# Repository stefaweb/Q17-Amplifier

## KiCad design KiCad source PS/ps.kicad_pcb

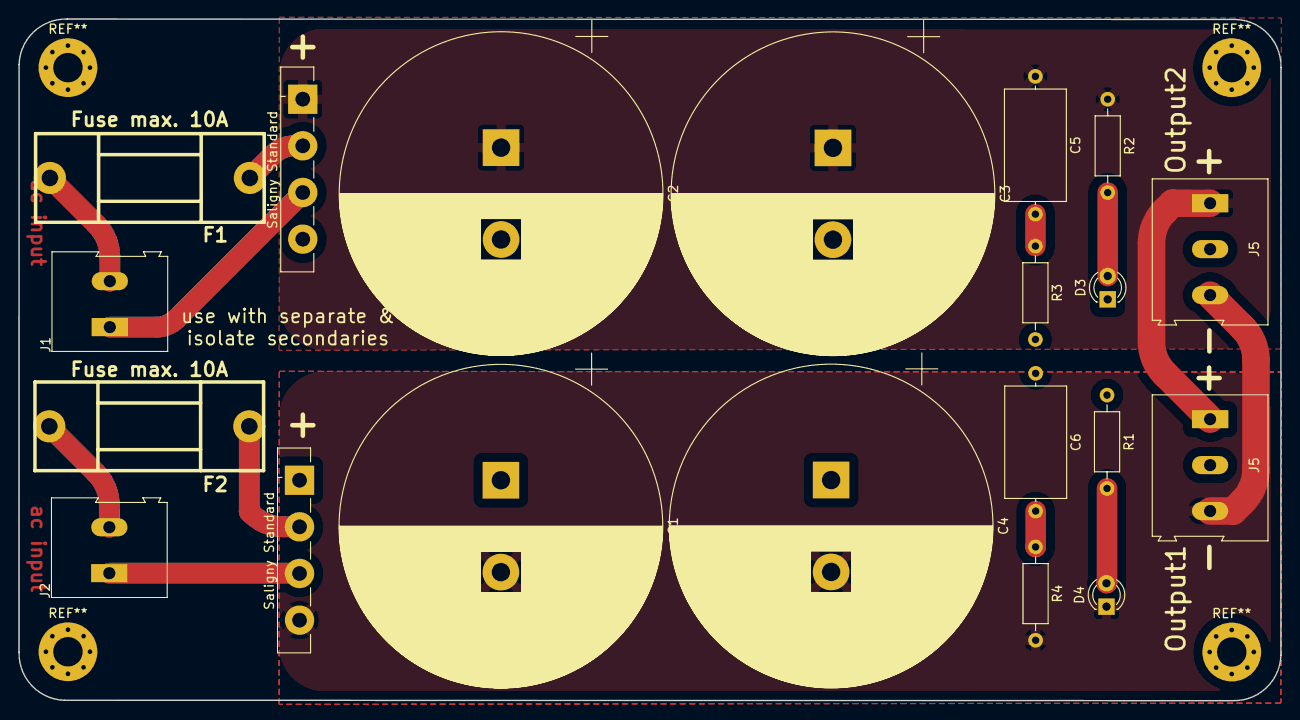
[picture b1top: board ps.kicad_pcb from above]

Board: 2 copper layers, 137.4 x 74.2 mm, 20 parts (0 on the bottom side), 11 nets.

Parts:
C1, C2, C3, C4: C_Polarized; CP_Radial_D35.0mm_P10.00mm_SnapIn
C5, C6: 220nF; C_Axial_L12.0mm_D6.5mm_P15.00mm_Horizontal
D3, D4: LED; LED_D3.0mm
F1, F2: Fuse max. 10A; fuse_holder_CQ-2
J1, J2: Conn_01x02_Female; TerminalBlock_Altech_AK300-2_P5.00mm
J5, J5#2: Conn_01x03_Female; TerminalBlock_Altech_AK300-3_P5.00mm
R1, R2: 10K; R_Axial_DIN0207_L6.3mm_D2.5mm_P10.16mm_Horizontal
R3, R4: 10; R_Axial_DIN0207_L6.3mm_D2.5mm_P10.16mm_Horizontal
Saligny Standard: Active_Bridge_+AA-; Diode_Bridge_Vishay_GBU
Saligny Standard#2: Active_Bridge_+AA-; Diode_Bridge_Vishay_GBU

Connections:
GNDPWR: C1.1, C2.2, C3.2, C4.1, C6.1, D3.1 (K), J5.2, J5#2.2, R1.1, R3.2, Saligny Standard.4 (-), Saligny Standard#2.1 (+)
unnamed: C5.2, R3.1
unnamed: C6.2, R4.1
unnamed: F1.2, Saligny Standard.2 (~~)
unnamed: J1.1, Saligny Standard.3 (~~)
unnamed: F2.2, Saligny Standard#2.2 (~~)
unnamed: J2.1, Saligny Standard#2.3 (~~)
unnamed: C1.2, C4.2, D4.1 (K), J5.3, J5#2.3, R4.2, Saligny Standard#2.4 (-)
unnamed: D3.2 (A), R2.2
unnamed: D4.2 (A), R1.2
unnamed: C2.1, C3.1, C5.1, J5.1, J5#2.1, R2.1, Saligny Standard.1 (+)

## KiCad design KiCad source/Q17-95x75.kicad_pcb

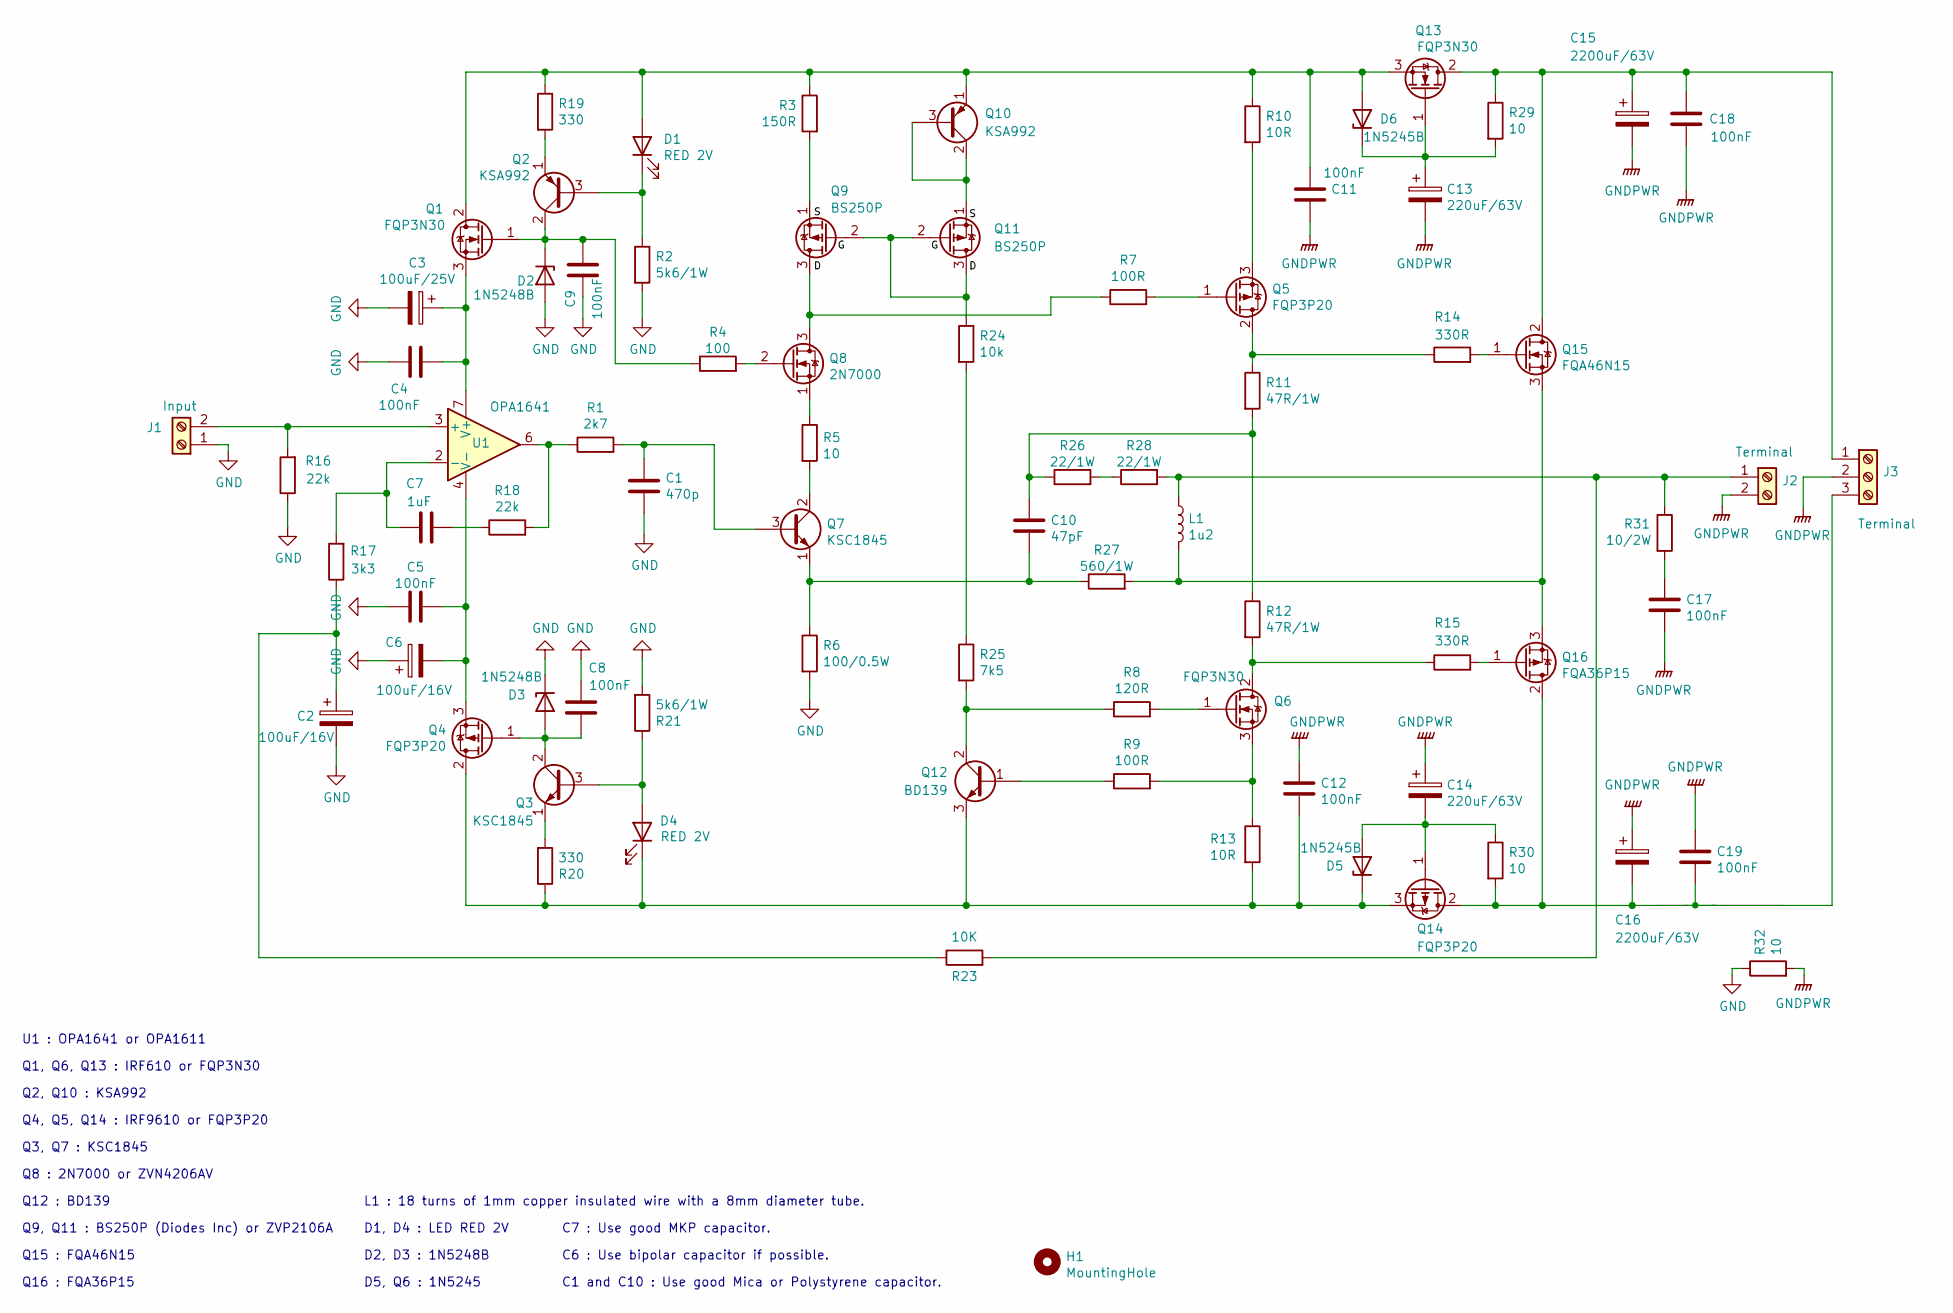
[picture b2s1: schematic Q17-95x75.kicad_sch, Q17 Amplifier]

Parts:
C1: 470p; C_Disc_D11.0mm_W5.0mm_P7.50mm
C2, C6: 100uF/16V; C_Radial_D10.0mm_H12.5mm_P5.00mm
C3: 100uF/25V; C_Radial_D10.0mm_H12.5mm_P5.00mm
C4, C5, C8, C9, C11, C12, C18, C19: 100nF; C_Disc_D7.5mm_W2.5mm_P5.00mm
C7: 1uF; CP_Axial_L26.5mm_D20.0mm_P33.00mm_Horizontal
C10: 47pF; C_Disc_D11.0mm_W5.0mm_P7.50mm
C13, C14: 220uF/63V; CP_Radial_D10.0mm_P5.00mm_P7.50mm
C15, C16: 2200uF/63V; CP_Radial_D18.0mm_P7.50mm
C17: 100nF; C_Rect_L18.0mm_W11.0mm_P15.00mm_FKS3_FKP3
D1, D4: RED 2V; LED_D5.0mm_Clear
D2, D3: 1N5248B; D_DO-35_SOD27_P7.62mm_Horizontal
D5, D6: 1N5245B; D_DO-35_SOD27_P7.62mm_Horizontal
H1: MountingHole; MountingHole_3.2mm_M3_Pad_Via
J1: Input; Stocko_MKS_1651-6-0-202_1x2_P2.50mm_Vertical
J2: Terminal; AMASS_XT30U-F_1x02_P5.0mm_Vertical
J3: Terminal; TerminalBlock_Altech_AK300-3_P5.00mm
L1: 1u2; L
Q1, Q6, Q13: FQP3N30; TO-220-3_Vertical
Q2, Q10: KSA992; TO-92
Q3, Q7: KSC1845; TO-92
Q4, Q5, Q14: FQP3P20; TO-220-3_Vertical
Q8: 2N7000; TO-92_Inline
Q9, Q11: BS250P; TO-92_Inline
Q12: BD139; TO-126-3_Vertical
Q15: FQA46N15; TO-3P-3_Horizontal_TabDown
Q16: FQA36P15; TO-3P-3_Horizontal_TabDown
R1: 2k7; R_Axial_DIN0207_L6.3mm_D2.5mm_P10.16mm_Horizontal
R2, R21: 5k6/1W; R_Axial_DIN0207_L6.3mm_D2.5mm_P10.16mm_Horizontal
R3: 150R; R_Axial_DIN0207_L6.3mm_D2.5mm_P10.16mm_Horizontal
R4: 100; R_Axial_DIN0207_L6.3mm_D2.5mm_P10.16mm_Horizontal
R5, R29, R30, R32: 10; R_Axial_DIN0207_L6.3mm_D2.5mm_P10.16mm_Horizontal
R6: 100/0.5W; R_Axial_DIN0207_L6.3mm_D2.5mm_P10.16mm_Horizontal
R7, R9: 100R; R_Axial_DIN0207_L6.3mm_D2.5mm_P10.16mm_Horizontal
R8: 120R; R_Axial_DIN0207_L6.3mm_D2.5mm_P10.16mm_Horizontal
R10, R13: 10R; R_Axial_DIN0207_L6.3mm_D2.5mm_P10.16mm_Horizontal
R11, R12: 47R/1W; R_Axial_DIN0411_L9.9mm_D3.6mm_P12.70mm_Horizontal
R14, R15: 330R; R_Axial_DIN0207_L6.3mm_D2.5mm_P10.16mm_Horizontal
R16, R18: 22k; R_Axial_DIN0207_L6.3mm_D2.5mm_P10.16mm_Horizontal
R17: 3k3; R_Axial_DIN0207_L6.3mm_D2.5mm_P10.16mm_Horizontal
R19, R20: 330; R_Axial_DIN0207_L6.3mm_D2.5mm_P10.16mm_Horizontal
R23: 10K; R_Axial_DIN0207_L6.3mm_D2.5mm_P10.16mm_Horizontal
R24: 10k; R_Axial_DIN0207_L6.3mm_D2.5mm_P10.16mm_Horizontal
R25: 7k5; R_Axial_DIN0207_L6.3mm_D2.5mm_P10.16mm_Horizontal
R26, R28: 22/1W; R_Axial_DIN0207_L6.3mm_D2.5mm_P10.16mm_Horizontal
R27: 560/1W; R_Axial_DIN0207_L6.3mm_D2.5mm_P10.16mm_Horizontal
R31: 10/2W; R_Axial_DIN0309_L9.0mm_D3.2mm_P12.70mm_Horizontal
U1: OPA1641; SOIC-8_3.9x4.9mm_P1.27mm

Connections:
GND: C1.2, C2.2, C3.2, C4.1, C5.1, C6.1, C8.1, C9.1, D2.2 (A), D3.1 (K), J1.1, R2.2, R6.2, R16.1, R21.2, R32.1
GNDPWR: C11.1, C12.1, C13.2, C14.1, C15.2, C16.1, C17.2, C18.1, C19.2, J2.2, J3.2, R32.2; also elsewhere on the board
unnamed: C1.1, Q7.3 (B), R1.2
unnamed: C2.1, R17.1, R23.1
unnamed 4: C3.1, C4.2, Q1.3 (S), U1.7 (V+); also elsewhere on the board
unnamed 5: C5.2, C6.2, Q4.3 (S), U1.4 (V-); also elsewhere on the board
unnamed: C8.2, D3.2 (A), Q3.2 (C), Q4.1 (G)
unnamed: C9.2, D2.1 (K), Q1.1 (G), Q2.2 (C), R4.1
unnamed: C10.1, R11.2, R12.1, R26.1
unnamed: C10.2, Q7.1 (E), R6.1, R27.1
unnamed: C11.2, D1.2 (A), D6.2 (A), Q1.2 (D), Q10.1 (E), Q13.3 (S), R3.1, R10.1, R19.1
unnamed: C12.2, D4.1 (K), D5.1 (K), Q4.2 (D), Q12.3 (E), Q14.3 (S), R13.2, R20.1
unnamed: C13.1, D6.1 (K), Q13.1 (G), R29.2
unnamed: C14.2, D5.2 (A), Q14.1 (G), R30.1
unnamed 14: C15.1, C18.2, J3.1, Q13.2 (D), Q15.2 (D), R29.1; also elsewhere on the board
unnamed 15: C16.2, C19.1, J3.3, Q14.2 (D), Q16.2 (D), R30.2; also elsewhere on the board
unnamed: C17.1, R31.2
unnamed: D1.1 (K), Q2.3 (B), R2.1
unnamed: D4.2 (A), Q3.3 (B), R21.1
unnamed 19: J1.2, R16.2, U1.3 (+); also elsewhere on the board
unnamed 20: J2.1, L1.1, R23.2, R28.2, R31.1; also elsewhere on the board
unnamed: L1.2, L1.3, Q15.3 (S), Q16.3 (S), R27.2
unnamed: Q2.1 (E), R19.2
unnamed: Q3.1 (E), R20.2
unnamed: Q5.1 (G), R7.2
unnamed: Q5.2 (D), R11.1, R14.1
unnamed: Q5.3 (S), R10.2
unnamed: Q6.1 (G), R8.2
unnamed: Q6.2 (D), R12.2, R15.1
unnamed: Q6.3 (S), R9.2, R13.1
unnamed: Q7.2 (C), R5.2
unnamed: Q8.1 (S), R5.1
unnamed: Q8.2 (G), R4.2
unnamed: Q8.3 (D), Q9.3 (D), R7.1
unnamed: Q9.1 (S), R3.2
unnamed: Q10.2 (C), Q10.3 (B), Q11.1 (S)
unnamed: Q9.2 (G), Q11.2 (G), Q11.3 (D), R24.1
unnamed: Q15.1 (G), R14.2
unnamed: Q16.1 (G), R15.2
unnamed 39: R1.1, R18.2, U1.6; also elsewhere on the board
unnamed: Q12.1 (B), R9.1
unnamed: R24.2, R25.1
unnamed: Q12.2 (C), R8.1, R25.2
unnamed: R26.2, R28.1

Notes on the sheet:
C1 and C10 : Use good Mica or Polystyrene capacitor.
Q12 : BD139
C7 : Use good MKP capacitor.
D2, D3 : 1N5248B
Q2, Q10 : KSA992
D1, D4 : LED RED 2V
Q3, Q7 : KSC1845
C6 : Use bipolar capacitor if possible.
Q4, Q5, Q14 : IRF9610 or FQP3P20
Q15 : FQA46N15
Q1, Q6, Q13 : IRF610 or FQP3N30
Q9, Q11 : BS250P (Diodes Inc) or ZVP2106A
U1 : OPA1641 or OPA1611
D5, Q6 : 1N5245
L1 : 18 turns of 1mm copper insulated wire with a 8mm diameter tube.
Q8 : 2N7000 or ZVN4206AV
Q16 : FQA36P15

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
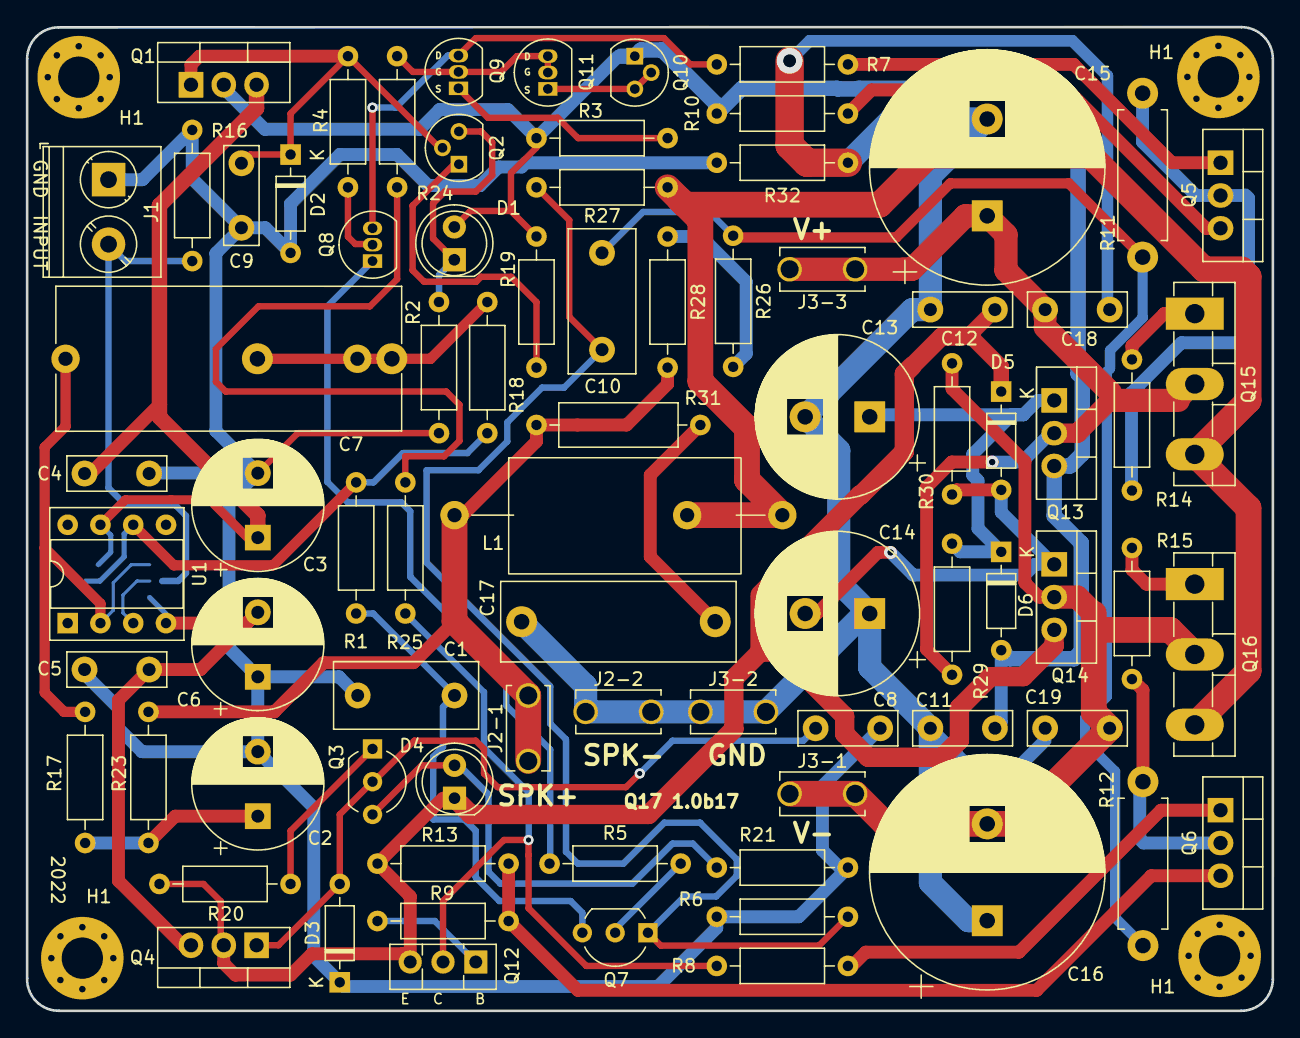
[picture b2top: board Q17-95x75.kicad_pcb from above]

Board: 2 copper layers, 96.5 x 76.2 mm, 85 parts (1 on the bottom side), 46 nets.

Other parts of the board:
Faston Connector: J3-1; Faston_connector
Faston Connector#2: J3-2; Faston_connector
Faston Connector#3: J2-1; Faston_connector
Faston Connector#4: J2-2; Faston_connector
Faston Connector#5: J3-3; Faston_connector
H1#2, H1#3, H1#4: MountingHole; MountingHole_3.2mm_M3_Pad_Via
U1#2: OPA1641; SOIC-8_3.9x4.9mm_P1.27mm

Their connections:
GNDPWR: Faston Connector#2.1, Faston Connector#2.2, Faston Connector#4.1, Faston Connector#4.2; also elsewhere on the board
unnamed 4: U1#2.7 (V+); also elsewhere on the board
unnamed 5: U1#2.4 (V-); also elsewhere on the board
unnamed 14: Faston Connector#5.1, Faston Connector#5.2; also elsewhere on the board
unnamed 15: Faston Connector.1, Faston Connector.2; also elsewhere on the board
unnamed 19: U1#2.3 (+); also elsewhere on the board
unnamed 20: Faston Connector#3.1, Faston Connector#3.2; also elsewhere on the board
unnamed 39: U1#2.6; also elsewhere on the board
